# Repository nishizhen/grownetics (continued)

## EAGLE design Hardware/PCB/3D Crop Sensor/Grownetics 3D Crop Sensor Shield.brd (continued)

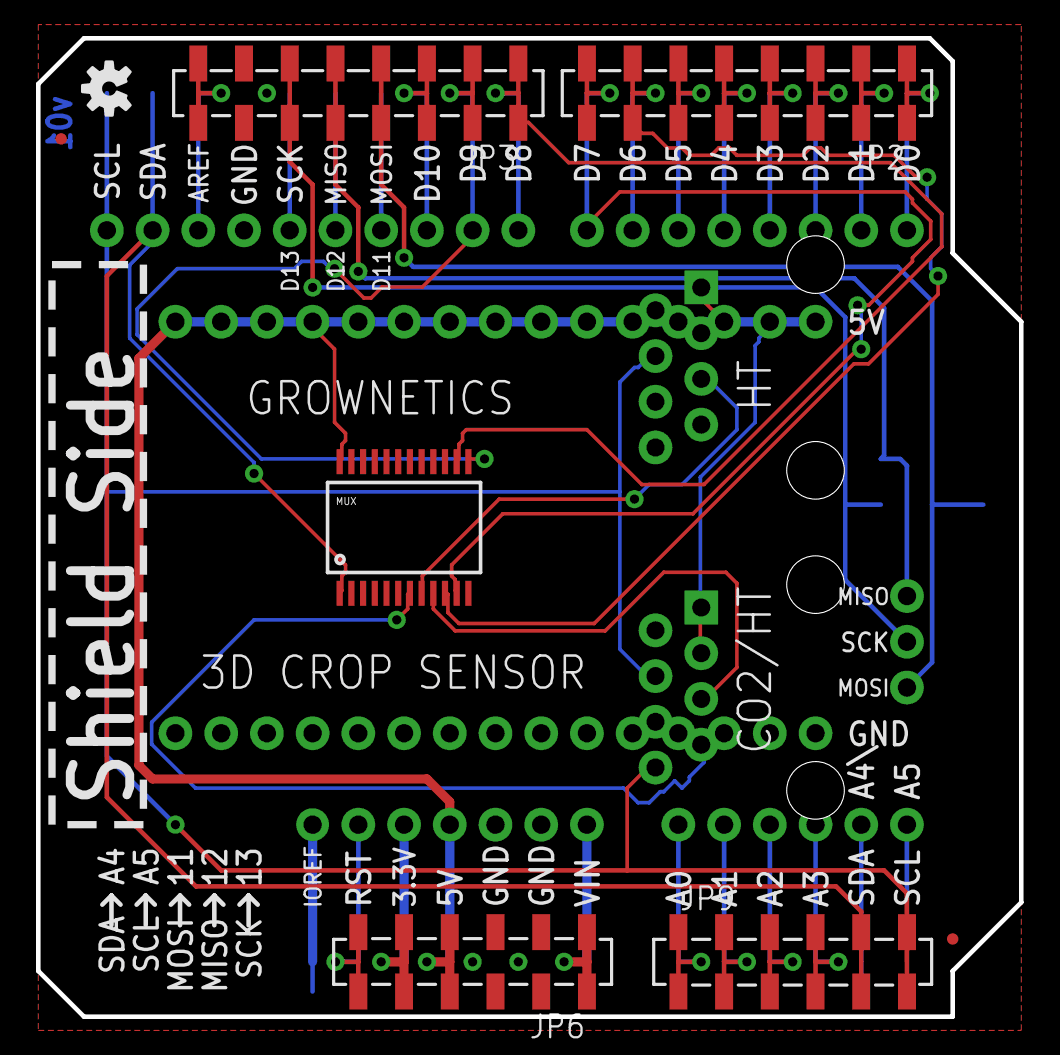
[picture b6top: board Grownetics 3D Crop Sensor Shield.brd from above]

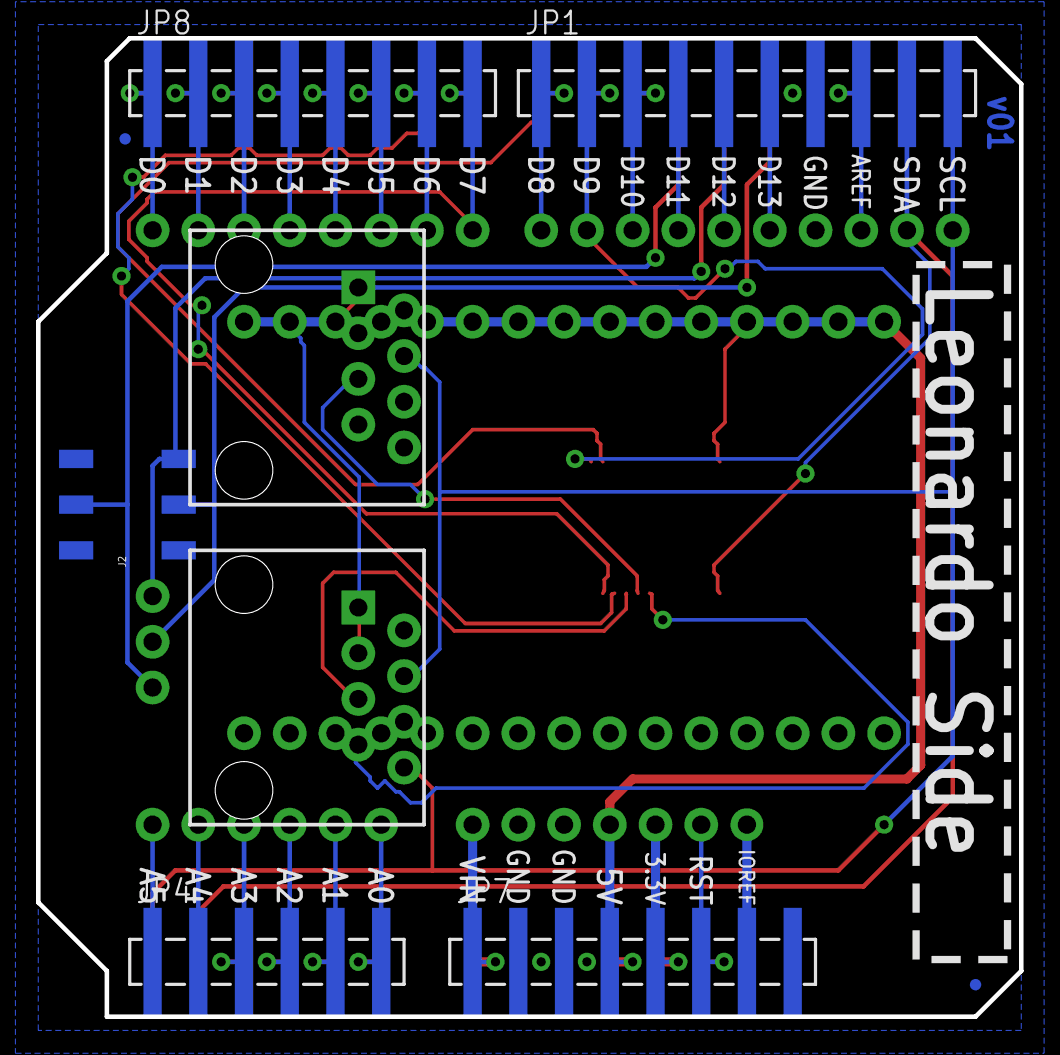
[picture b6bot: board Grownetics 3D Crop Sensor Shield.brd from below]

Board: 2 copper layers, 54.6 x 54.4 mm, 17 parts (9 on the bottom side), 29 nets.

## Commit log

2019-07-02 Add LICENSE
2019-07-02 Initial open source code dump
2019-07-02 Removing fluff
2019-07-12 Closes #2 - Users can belong to multiple roles
2019-07-18 Resolve "Users should be able to create organizations and invite other users"
2019-07-18 Adding LICENSE
2019-07-18 Add env var
2019-07-19 Disable organizations when ONSITE is true
2019-07-19 Test script cleanup
2019-07-19 Formatting
2019-07-19 UsersRoles seed and fixture
2019-07-19 VSCode and docs
2019-07-19 Env var and test fixs
2019-07-22 OrganizationBehavior fixes, test fixes
2019-07-22 Resolve "Add ENV var to disable Organizations"
2019-07-23 Temp stuff
2019-07-26 Tasks controller fix
2019-07-26 Tasks fix
2019-09-04 Allow moving batches into zones with no plant placeholders
2019-10-25 Moving to MIT
2019-10-25 Adding community links
2019-10-25 CI test
2019-10-25 New Message
2019-10-25 Add new file
2019-10-29 CI fix
2019-10-30 Moving from old code. addresses
2019-10-30 Remove old doc
2019-10-30 Remove old docs
2019-10-30 Setting up gitlab pages
2019-10-30 CI docker fix
2019-10-30 Gitlab ci
2019-10-30 Pages fix attempt
2019-10-30 Removing old info
2019-10-30 CI fix attempt
2019-11-13 Updating to new public image location
2019-11-13 Update contributing doc
2019-12-03 Docs update
2019-12-12 Resolve "Fix pipes."
2019-12-12 Pipes
2019-12-13 Pages
2019-12-13 Handbook
2019-12-13 Clean up pages deploy
2020-01-17 Resolve "Fix Review Apps"
2020-01-17 Qa.env re-add
2020-01-21 Updated handbook Quick Links section
2020-01-21 Update Handbook/documentation.md, Handbook/index.md files
2020-01-22 Handbook deploy/pages fix
2020-01-22 Docs updates
2020-01-27 Kinda working
2020-01-31 Updated handbook, getting on that handbook first.
2020-01-31 Cleaning up.
2020-02-03 Handbook first update.
2020-02-03 re-arranging page
2020-02-03 Editing to be explicitly about sales vs Biz Dev (which it was merged with before).
2020-02-04 Add edit link to docs
2020-02-04 Image build fixes
2020-02-11 Update tools page
2020-02-12 Adding softmax python recommender first cut
2020-02-12 Working softmax beyond 4 rooms
2020-02-13 softmax readme improvement
2020-02-13 softmax readme
2020-02-13 Update Handbook - How We Work.md with wrike section.
2020-02-13 Update handbook how we work pages
2020-02-18 handbook update - formatting
2020-02-18 Updated doc formatting index.md
2020-02-19 added QA link to QA docs
2020-02-21 Readme update
2020-02-21 Adding macrofab documentation
2020-02-21 Updating link to docs
2020-02-21 Formatting README
2020-02-21 Adding getting started
2020-02-21 URL fix
2020-02-21 fixed broken sales link.
2020-02-21 Added start of project delivery section
2020-02-21 Starting how to create an integration plan docs.
2020-02-21 spelling
2020-02-25 Renamed safety.md to on-site-safety.md added electrical section
2020-02-25 Added vendor sourcing update
2020-02-26 Renamed on-call to support.md added hardware audit section
2020-02-26 Update support docs for sensor troubleshooting.
2020-03-03 Updated meetings.md to include our regular meeting types and their purpose.
2020-03-03 Updated meetings.md
2020-03-03 Added daily kickoff checklist to How we work.md
2020-03-04 Adding plant id standard to docs
2020-03-06 Dockerfile fix attempt
2020-03-10 Added MNDA how to
2020-03-10 added new doc on MNDA's to mkdocs menu.
2020-03-12 Updating README links
2020-03-12 Docker build fix
2020-03-12 Remove extra CI step
2020-03-16 Updated Meetings.md to move L10 to Tues and change project review meeting back to client projcect review meeting since that alone takes all morning.
2020-03-24 Multi arch attempt 1
2020-03-24 MultiArch Test 2
2020-03-24 MultiArch Test 3
2020-03-24 MultiArch Test 4
2020-03-24 MultiArch Test 5
2020-03-27 Adding inital social post template
2020-04-13 Having seed script create cache directories
2020-04-13 Floorplan bug fixes
2020-04-15 Adding static website
2020-04-15 Website update
2020-04-15 Website
2020-04-15 Static website fixes, add Makefile
2020-04-15 Makefile fix
2020-04-15 Adding web_serve makefile command
2020-04-20 Fix for wipe floorplan button
2020-04-20 Dont require a floorplan to load the dash
2020-04-22 Pipeline and seed fix
2020-05-05 Fix growpulse potential memory leak
2020-05-05 Adding integrations manager w/ infisense
2020-05-13 Backup restore fixes
2020-05-13 Getting everything in
2020-05-18 Adding main.go back
2020-05-18 Tagging dev versions
2020-05-18 Remove growctl build step for now
2020-05-18 Cleaner ci flow
2020-05-18 Adding restic to the php image
2020-05-18 Adding php build
2020-06-05 Set point for target fix
2020-06-24 Removing old wiki link from nav
2020-06-24 Fixing seed to use envvars
2020-06-29 Salt fix
2020-07-01 Remove bookstack from our compose
2020-07-05 Zulip env vars
2020-07-05 Notifications index fix
2020-07-05 Consul host fix
2020-07-05 Consul host
2020-07-05 Seed influx fix
2020-07-05 Server env vars
2020-07-05 Remove rancher labels
2020-07-05 Better messaging for new batches without cultivars
2020-07-05 Backups info
2020-07-05 Temporarily disable storing output schedule statuses
2020-07-05 Update login bg
2020-07-08 Fix for dash map using remote_url and port
2020-07-08 Remove grafana link from nav
2020-07-08 Remote domain/url fix
2020-07-08 Migrate to REMOTE_DOMAIN
2020-08-28 Don't auto create tables on user creation
2020-08-28 Adding 1.2 crop sensor
2020-08-28 Watchdog for crop sensor
2020-08-28 Docker-compose fixes
2020-08-28 Dash map+import fixes
2020-08-28 Improved debugging for import, new sensor types
2020-08-28 Api + floorplan tweaks
2020-08-29 Typo fix
2020-08-29 Floorplan admin menu display fix
2020-09-17 Floorplans add fix
2020-09-21 Port fix
2020-09-21 Temp disable caching of sensors
2020-10-07 Map sensor color fix
2020-10-07 Map temperature conversions for new sensor types
2020-11-02 Updating socket.io inclusion URL for HomelabOS deploy
2020-11-06 System health fixes
2020-11-06 Cleanup
2020-11-06 Add .env to gitignore
2020-11-06 Bacnet docs
2020-11-06 Remove piwik, switch socket based on Dev
2020-11-06 Format
2020-11-13 Infisense fixes
2020-11-13 Socket fix
2020-11-13 LoRa
2020-11-14 Debug cleanup
2020-11-14 Plant placeholder cleanup
2020-11-16 Infisense backfill
2020-11-25 Configs
2020-11-25 Debugging
2020-11-25 Temporary notes/photos fix
2020-11-30 Xdebug build fix
2020-12-01 Add fixes
2020-12-01 Floorplan import clear redirect to import
2020-12-01 Correctly associating zones with devices, and map_item_types for devices
2020-12-01 Fix for associating map items to zones
2020-12-01 Build fixes
2020-12-02 Devices associated with zones on import
2020-12-02 Remove caching of files for growdash dev
2020-12-02 Make sure Sensor mapitemtype exists
2020-12-03 Fix for room_zones on import
2020-12-03 Fix for moving plants
2020-12-03 Store data_type and sensor_type separate for zone datapoints
2020-12-04 Dash chart fix for data_type
2020-12-07 Uploads, roles, and infisense fixes.
2020-12-09 Hide unsortable fields
2020-12-14 Setup docs
2021-01-04 Influx creds
2021-01-13 Importing placeholders and other floorplan layers by batches
2021-01-25 Allow non-numeric api IDs for devices
2021-01-25 Device API field type
2021-01-28 Store sensor_type and data_type consistently
2021-02-02 Disable placeholders on dash for now
2021-02-02 Firmware Updates
2021-02-03 Data points fix
2021-02-11 Removing sensor edit/add zones field
2021-02-13 sematic versioned the scd30 library due to memory issues, changed BME Yes/No to Y/N
2021-02-17 Soil moisture
2021-03-02 Infisense api fix
2021-03-04 Infisense SEEEED fix
2021-03-05 Infisense fix
2021-04-09 Firmware update 1.4 turns on autocalibration and sets scd30 continuous logging mode
2021-04-20 Edit device zones
2021-05-12 Calibration temporary fix
2021-06-02 VPD zone data fix
2021-07-08 Calibration fix
2021-07-08 Calibration revert
2021-07-14 Rounding
2021-07-14 Rounding sensor types also
2021-07-14 Round everything.
2021-09-02 Map hack fix
2021-09-03 Floorplan colors
2021-09-14 Infisense API fixes
2021-10-20 Map data overlay fix
2021-10-20 Redirect to device page after deleting sensor
2021-10-20 Make empty sensors translucent
2021-10-20 Add device id to sensor label for infisense
2021-10-20 added new infisense sensors
2021-10-21 Added new sensor types
2021-10-21 Added map gradients for new sensors
2021-10-21 Added gradient breaks for new sensor types
2021-10-21 commas
2021-10-22 Update map device gradients to match data_type
2021-11-02 Show completed tasks
2021-11-02 Acl fix
2022-01-08 Save median and mode
2022-01-08 averaging
2022-05-09 Fix wireless sensor units not displaying on map
2022-05-09 Added new sensors to sensor_type, data type
2022-05-10 Added new infisense sensor gradients, adjusted PAR gradients
2022-05-10 Added LoRa water_depth data type
